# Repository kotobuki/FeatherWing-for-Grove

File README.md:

# FeatherWing for Grove

A bridge between the [**Grove**](http://www.seeedstudio.com/wiki/Category:Grove) family by the Seeed Studio and [**Feather**](https://www.adafruit.com/feather) by the Adafruit Industries.

## Bill of Materials

|Part/Designator|Manufacture Part Number/Seeed SKU|Quantity|
|---------------|---------------------------------|--------|
|PCB||1|
|J1|Digi-Key: [S1011EC-12-ND](http://www.digikey.com/product-search/en?keywords=S1011EC-12-ND)|1||J2|Digi-Key: [S1011EC-16-ND](http://www.digikey.com/product-search/en?keywords=S1011EC-16-ND)|1||J3,J4,J5,J6|Seeed SKU: [320110033](http://www.seeedstudio.com/depot/index.php?main_page=opl_info&opl_id=4)|4||SW1|Seeed SKU: [311030001](http://www.seeedstudio.com/depot/index.php?main_page=opl_info&opl_id=625)|1|

## How to 'Compile'?

Place an order at the [Fusion PCBA prototype](http://www.seeedstudio.com/service/index.php?r=pcb) service.

## Compatible Grove Modules

* Sensors
  * [Grove - Switch(P)](http://www.seeedstudio.com/wiki/Grove_-_Switch(P))
  * [Grove - Rotary Angle Sensor](http://www.seeedstudio.com/wiki/Grove_-_Rotary_Angle_Sensor)
  * [Grove - Slide Potentiometer](http://www.seeedstudio.com/wiki/Grove_-_Slide_Potentiometer)
  * [Grove - Touch Sensor](http://www.seeedstudio.com/wiki/Grove_-_Touch_Sensor)
  * [Grove - Light Sensor](http://www.seeedstudio.com/wiki/Grove_-_Light_Sensor)
  * [Grove - Single Axis Analog Gyro](http://www.seeedstudio.com/wiki/Grove_-_Single_Axis_Analog_Gyro)
  * [Grove - Button](http://www.seeedstudio.com/wiki/Grove_-_Button)
  * [Grove - Q Touch Sensor](https://seeedstudio.com/Grove-Q-Touch-Sensor-p-1854.html)
* Actuators
  * [Grove - LED Socket Kit](http://www.seeedstudio.com/wiki/Grove_-_LED)
  * [Grove - Buzzer](http://www.seeedstudio.com/wiki/Grove_-_Buzzer)
  * [Grove - Vibration Motor](http://www.seeedstudio.com/wiki/Grove_-_Vibration_Motor)
  * [Grove - Servo](http://www.seeedstudio.com/wiki/Grove_-_Servo)

# License Information

This design document is licensed by Shigeru Kobayashi under the terms of the [Creative Commons Attribution-ShareAlike 4.0 International Public License](http://creativecommons.org/licenses/by-sa/4.0/).

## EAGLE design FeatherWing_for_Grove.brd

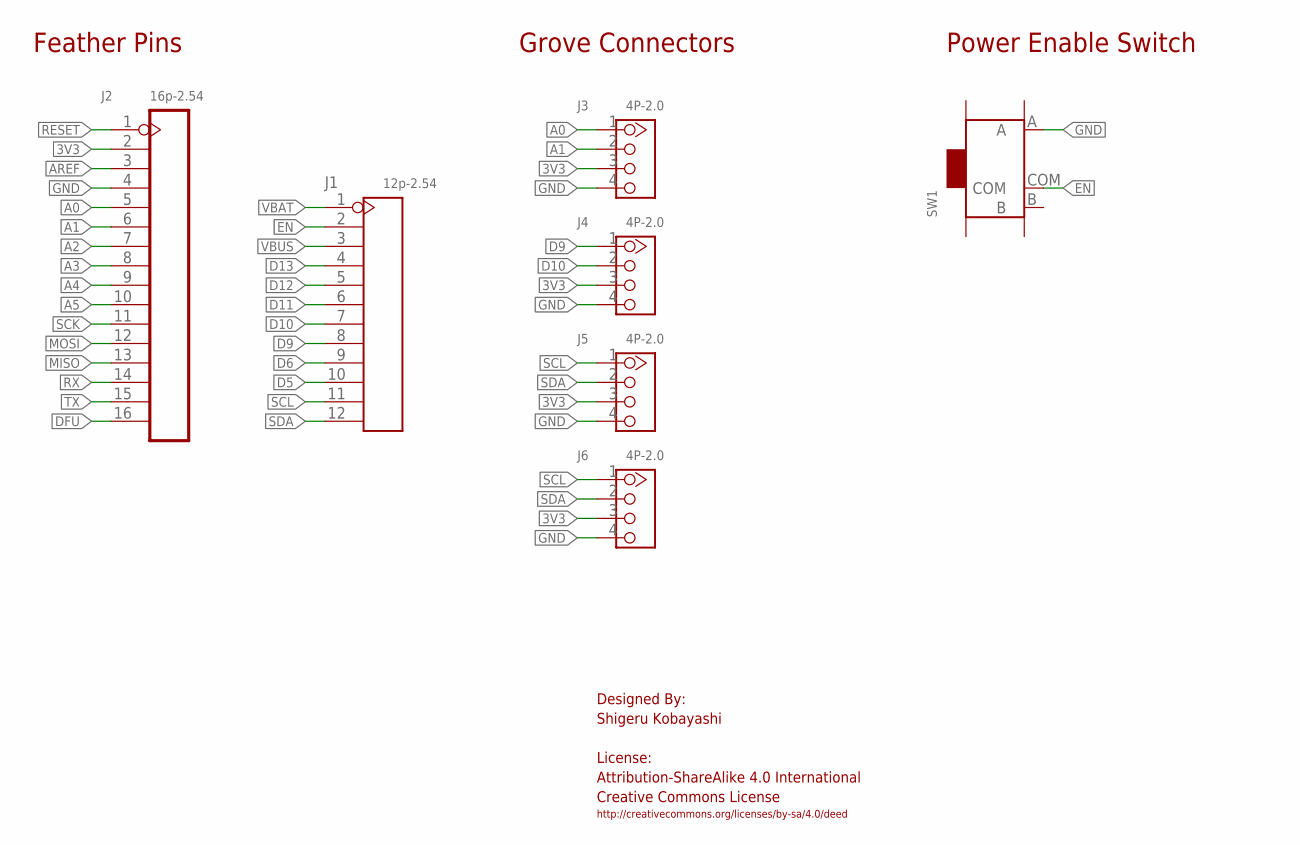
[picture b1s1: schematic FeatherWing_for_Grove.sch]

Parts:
J1: 12p-2.54; H12-2.54
J2: 16p-2.54; H16-2.54
J3, J4, J5, J6: 4P-2.0; HW4-2.0
SW1: SMD-TOGGLE-SWITCH-ON-ON(3+4P-6.7X2.7MM); SW7-SMD-L6.7X2.7X3.2MM

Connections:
3V3: J2.2, J3.3, J4.3, J5.3, J6.3
A0: J2.5, J3.1
A1: J2.6, J3.2
A2: J2.7
A3: J2.8
A4: J2.9
A5: J2.10
AREF: J2.3
D5: J1.10
D6: J1.9
D9: J1.8, J4.1
D10: J1.7, J4.2
D11: J1.6
D12: J1.5
D13: J1.4
DFU: J2.16
EN: J1.2, SW1.COM
GND: J2.4, J3.4, J4.4, J5.4, J6.4, SW1.A
MISO: J2.13
MOSI: J2.12
RESET: J2.1
RX: J2.14
SCK: J2.11
SCL: J1.11, J5.1, J6.1
SDA: J1.12, J5.2, J6.2
TX: J2.15
VBAT: J1.1
VBUS: J1.3

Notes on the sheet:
Feather Pins
Grove Connectors
Power Enable Switch
Designed By: Shigeru Kobayashi License: Attribution-ShareAlike 4.0 International Creative Commons License
http://creativecommons.org/licenses/by-sa/4.0/deed

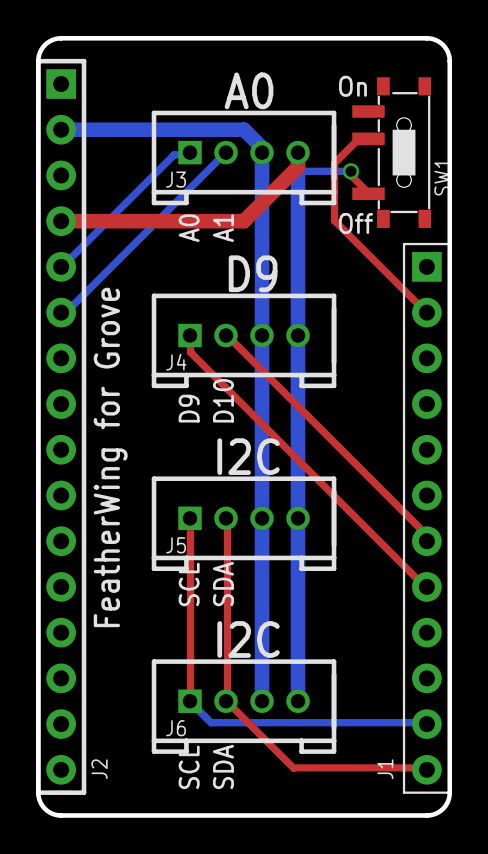
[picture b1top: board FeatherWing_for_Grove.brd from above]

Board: 2 copper layers, 22.9 x 43.2 mm, 7 parts (0 on the bottom side), 9 nets.

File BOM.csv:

Part/Designator,Manufacture Part Number/Seeed SKU,QuantityJ1,PRPC012SAAN-RC,1J2,PRPC016SAAN-RC,1"J3,J4,J5,J6",320110033,4SW1,311030001,1

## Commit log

2016-08-20 Add an image
